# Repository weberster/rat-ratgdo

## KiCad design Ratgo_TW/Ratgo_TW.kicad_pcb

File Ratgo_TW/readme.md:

PCB Workflow with Bouni’s Plugin and easyeda2kicad
This guide explains how to set up Bouni’s KiCad JLCPCB Tools and easyeda2kicad when designing PCBs for JLCPCB assembly.
It’s written for beginners new to electronic design workflows using KiCad 8.

Overview
You’ll use:

Bouni’s KiCad JLCPCB Tools → integrates with KiCad to generate JLCPCB‑ready BOM and placement files.

easyeda2kicad → converts LCSC (JLCPCB) components into KiCad‑ready symbols, footprints, and 3D models.

Step 1: Install Python and Pip
macOS / Linux
python3 -m ensurepip --upgrade
pip3 --version

Windows
Download from python.org and check Add Python to PATH during installation.

Step 2: Install easyeda2kicad
pip install easyeda2kicad

If you see warnings like:
WARNING: The script easyeda2kicad is installed in '/Users/you/Library/Python/3.9/bin'

Add that directory to your PATH (for zsh):

echo 'export PATH=$PATH:/Users/you/Library/Python/3.9/bin' >> ~/.zshrc
source ~/.zshrc

Step 3: Generate KiCad Libraries
Each JLCPCB part has an LCSC ID (e.g., C2040).
Run this command to generate full KiCad libraries for that part:

easyeda2kicad --full --lcsc_id=C2040

You can customize the output folder:

easyeda2kicad --full --lcsc_id=C2040 --output ~/KiCad/libs/my_parts

Generated files include:
my_parts.kicad_sym # symbols
my_parts.pretty/ # footprints
my_parts.3dshapes/ # 3D models

Step 4: Add the Libraries into KiCad
Add Symbol Library
Preferences → Manage Symbol Libraries → Global

Add: ${EASYEDA2KICAD}/easyeda2kicad.kicad_sym

Add Footprint Library
Preferences → Manage Footprint Libraries → Global

Add: ${EASYEDA2KICAD}/easyeda2kicad.pretty

Step 5: Install Bouni’s JLCPCB Tools Plugin
Open KiCad → Tools → Plugin and Content Manager

Click Manage Repositories → + → Add URL:
https://raw.githubusercontent.com/Bouni/bouni-kicad-repository/main/repository.json

Switch to Bouni’s Repository in the dropdown.

Locate KiCad JLCPCB Tools → click Install.

Apply changes and restart KiCad.

You should now see a blue JLC icon in the PCB Editor toolbar.

Step 6: Assign LCSC Numbers & Export
In your schematic, add a field named “LCSC”.

Enter each component’s LCSC ID (e.g., C2040).

With footprints assigned, open PCB Editor → Bouni’s Plugin.

Generate:

BOM (Bill of Materials)

CPL (Pick‑and‑Place)

These files are formatted for JLCPCB assembly upload.

Step 7: Upload to JLCPCB
When ordering at JLCPCB.com, upload:

Gerber files

BOM file

CPL file

Their assembly service matches your parts automatically using LCSC IDs.

Additional Tips
Regenerate specific parts anytime:
easyeda2kicad --footprint --3d --lcsc_id=C2040 --overwrite

Always verify footprint orientation before finalizing.

Keep libraries organized in a global KiCad path for reuse.

Credits
Bouni’s Plugin: https://github.com/Bouni/kicad-jlcpcb-tools

easyeda2kicad: https://github.com/uPesy/easyeda2kicad.py

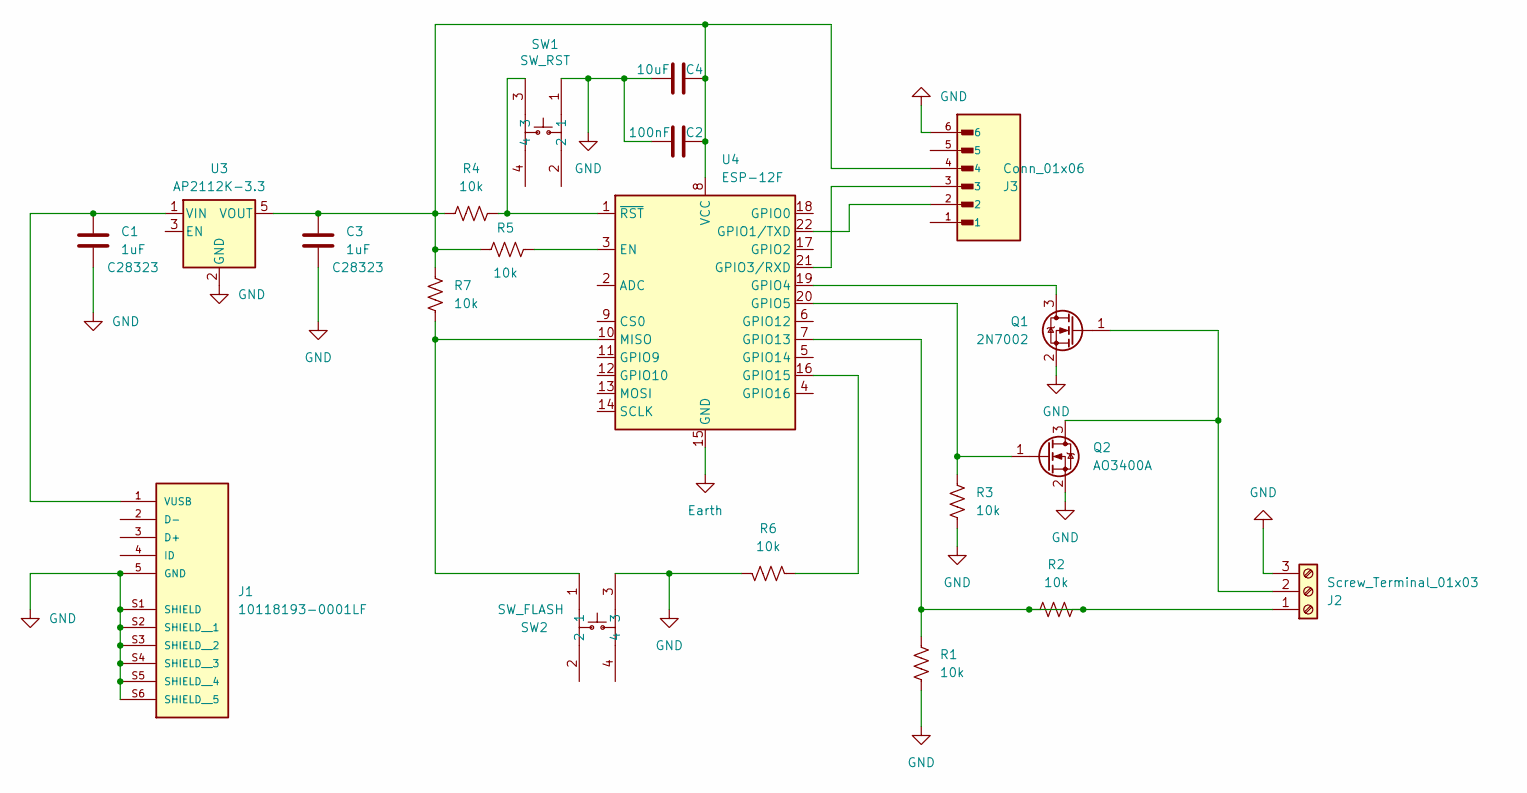
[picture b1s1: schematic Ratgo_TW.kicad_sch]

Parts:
C1, C3: 1uF; C_0805_2012Metric; JLCPCB P/N C28323
C2: 100nF; C_0805_2012Metric
C4: 10uF; C_0805_2012Metric
J1: 10118193-0001LF; AMPHENOL_10118193-0001LF; PARTREV E
J2: Screw_Terminal_01x03; TB006-508-03BE
J3: Conn_01x06; METZ-CONNECT_PR20206VBNN; PARTREV Y
Q1: 2N7002; SOT-23
Q2: AO3400A; SOT-23
R1, R2, R3, R4, R5, R6, R7: 10k; R_0805_2012Metric
SW1: SW_RST; SW-SMD_4P-L6.2-W6.2-P4.00-LS6.8; LCSC Part C115354
SW2: SW_FLASH; SW-SMD_4P-L6.2-W6.2-P4.00-LS6.8; LCSC Part C115354
U3: AP2112K-3.3; SOT-23-5
U4: ESP-12F; ESP-12E

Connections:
Earth: U4.15 (GND)
GND: C1.2, C2.1, C3.2, C4.1, J1.5 (GND), J1.S1 (SHIELD), J1.S2 (SHIELD__1), J1.S3 (SHIELD__2), J1.S4 (SHIELD__3), J1.S5 (SHIELD__4), J1.S6 (SHIELD__5), J2.3, J3.6, Q1.2 (S), Q2.2 (S), R1.1, R3.1, R6.1, SW1.1, SW2.3, U3.2 (GND)
unnamed: C1.1, J1.1 (VUSB), U3.1 (VIN)
unnamed: J2.1, R1.2, R2.1, R2.2, U4.7 (GPIO13)
unnamed: J2.2, Q1.1 (G), Q2.3 (D)
unnamed: Q1.3 (D), U4.19 (GPIO4)
unnamed: Q2.1 (G), R3.2, U4.20 (GPIO5)
unnamed: C2.2, C3.1, C4.2, J3.4, R4.1, R5.1, R7.1, U3.5 (VOUT), U4.8 (VCC)
unnamed: R5.2, U4.3 (EN)
unnamed: J3.2, U4.22 (GPIO1/TXD)
unnamed: J3.3, U4.21 (GPIO3/RXD)
unnamed: R6.2, U4.16 (GPIO15)
unnamed: R7.2, SW2.1, U4.10 (MISO)
unnamed: R4.2, SW1.3, U4.1 (~RST)

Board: 2 copper layers, 20 parts (0 on the bottom side), 13 nets, no tracks yet.

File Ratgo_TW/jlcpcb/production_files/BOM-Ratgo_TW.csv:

Comment,Designator,Footprint,LCSC,Quantity
100nF,C2,C_0805_2012Metric,C28233,1
10118193-0001LF,J1,AMPHENOL_10118193-0001LF,C132562,1
10k,"R1,R2,R3,R4,R5,R6,R7",R_0805_2012Metric,C17414,7
10uF,C4,C_0805_2012Metric,C15850,1
1uF,"C1,C3",C_0805_2012Metric,C28323,2
2N7002,Q1,SOT-23,C8545,1
AO3400A,Q2,SOT-23,C20917,1
AP2112K-3.3,U3,SOT-23-5,C51118,1
Conn_01x06,J3,HDR-TH_6P-P2.54-V-M-1,C37208,1
ESP-12F,U4,ESP-12E,C82891,1
SW_FLASH,SW2,SW-SMD_4P-L6.2-W6.2-P4.00-LS6.8,C115354,1
SW_RST,SW1,SW-SMD_4P-L6.2-W6.2-P4.00-LS6.8,C115354,1
Screw_Terminal_01x03,J2,CONN-TH_3P-P5.08_1729131,C91154,1

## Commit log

2025-10-11 hello
2025-10-21 latest with all footprints
2025-10-26 read me for easyeda conversion
2025-10-26 better readme
2025-11-18 release 1.0 to JLCPCB
